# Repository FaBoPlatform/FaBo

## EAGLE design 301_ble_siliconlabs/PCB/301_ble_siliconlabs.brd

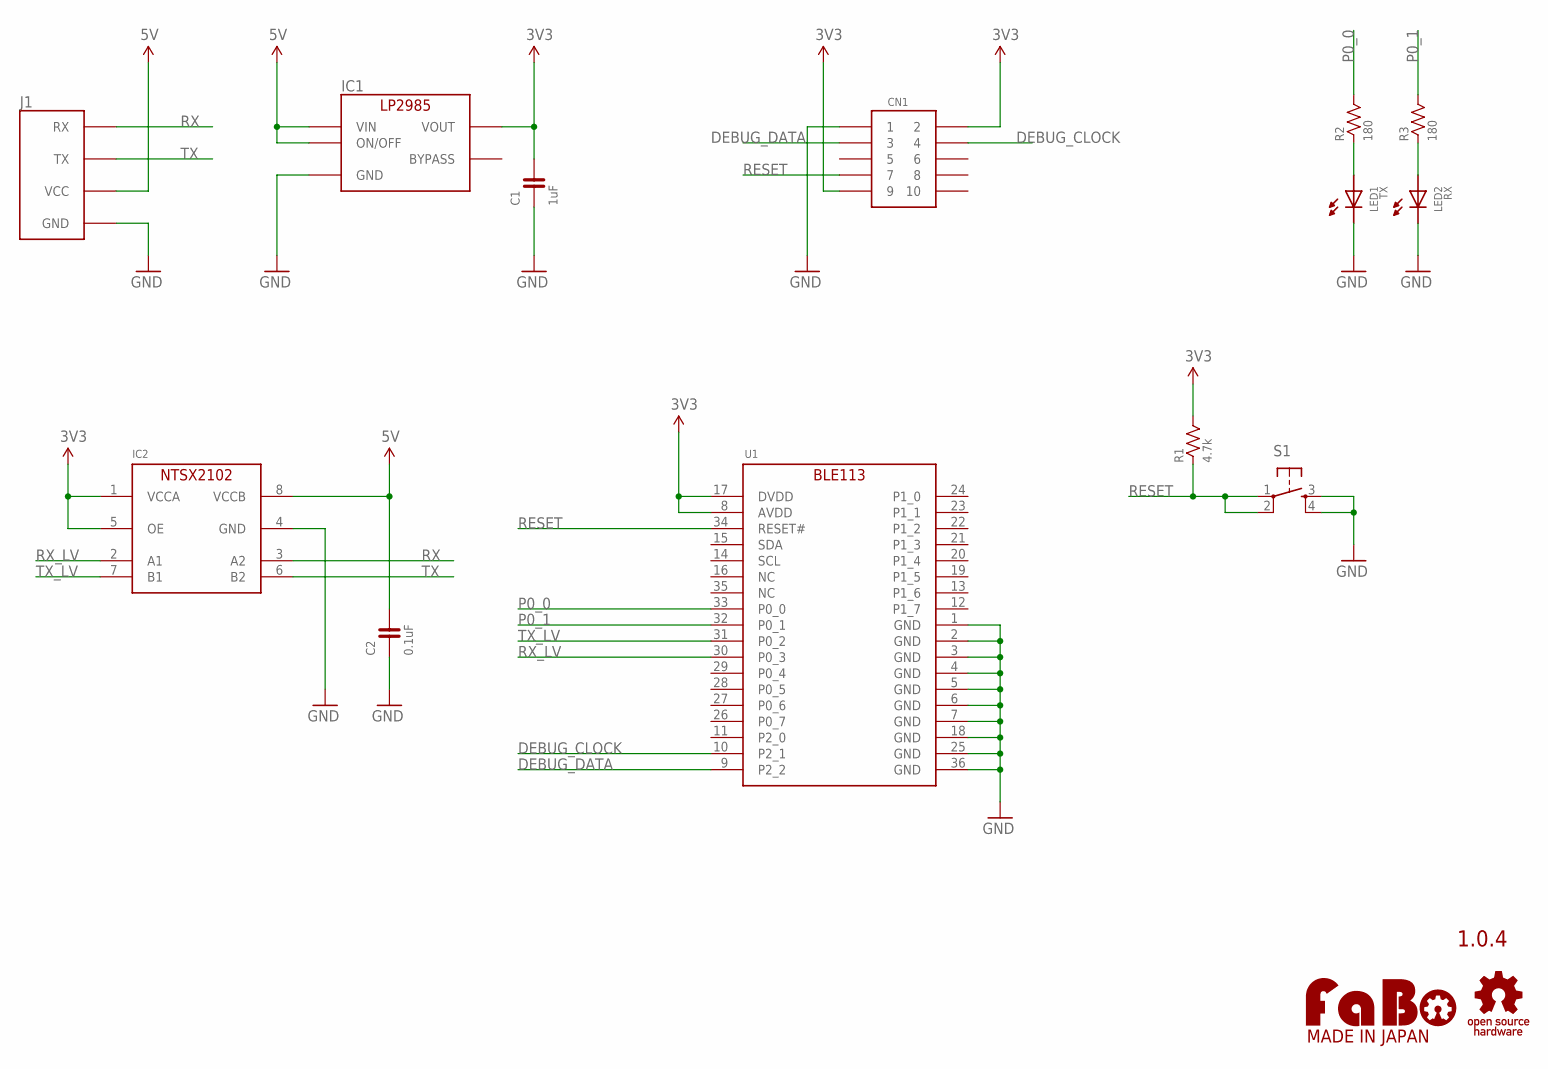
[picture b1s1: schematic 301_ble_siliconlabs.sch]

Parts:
C1: 1uF; 0603
C2: 0.1uF; 0603
CN1: PIN-HEADER-SMT(1.27MM)2X5
IC1: LP2985-33DBV; SOT-23-5
IC2: NTSX2102GU8H; SOT1309-1
J1: FABO_BRICK_SERIAL
LED1: TX; 0603
LED2: RX; 0603
R1: 4.7k; 0603
R2, R3: 180; 0603
S1: TACT-SWITCH-SMD_KMR2; KMR2
U1: BLUEGIGA-BLE113
U$2: LOGO_OSHW-M_BOTTOM; LOGO_OSHW_M_BOTTOM
U$3: LOGO_FABO-M_BOTTOM; LOGO_FABO_MS_BOTTOM

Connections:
3V3: C1.2, CN1.2, CN1.9, IC1.5 (VOUT), IC2.1 (VCCA), IC2.5 (OE), R1.2, U1.8 (AVDD), U1.17 (DVDD)
5V: C2.2, IC1.1 (VIN), IC1.3 (ON/OFF), IC2.8 (VCCB), J1.VCC
DEBUG_CLOCK: CN1.4, U1.10 (P2_1)
DEBUG_DATA: CN1.3, U1.9 (P2_2)
GND: C1.1, C2.1, CN1.1, IC1.2 (GND), IC2.4 (GND), J1.GND, LED1.CATHODE, LED2.CATHODE, S1.3, S1.4, U1.1 (GND), U1.2 (GND), U1.3 (GND), U1.4 (GND), U1.5 (GND), U1.6 (GND), U1.7 (GND), U1.18 (GND), U1.25 (GND), U1.36 (GND)
unnamed: LED1.ANODE, R2.1
unnamed: LED2.ANODE, R3.1
P0_0: R2.2, U1.33 (P0_0)
P0_1: R3.2, U1.32 (P0_1)
RESET: CN1.7, R1.1, S1.1, S1.2, U1.34 (RESET#)
RX: IC2.3 (A2), J1.RX
RX_LV: IC2.2 (A1), U1.30 (P0_3)
TX: IC2.6 (B2), J1.TX
TX_LV: IC2.7 (B1), U1.31 (P0_2)

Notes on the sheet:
1.0.4

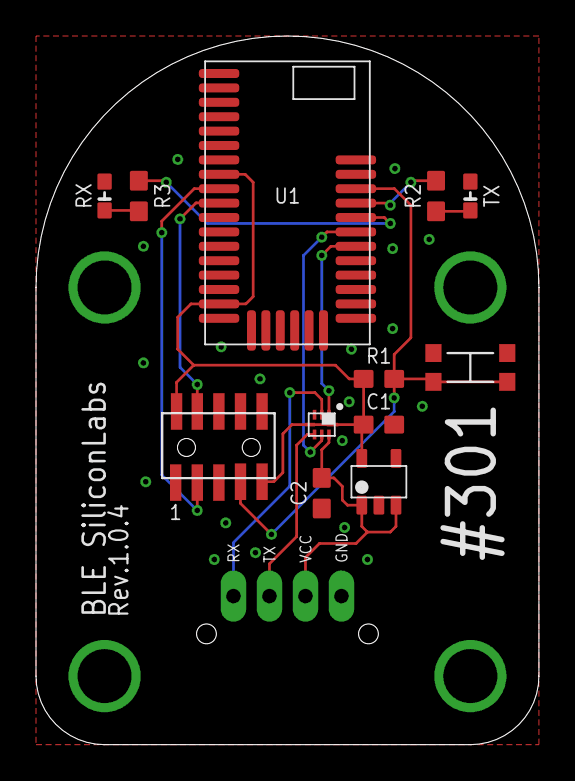
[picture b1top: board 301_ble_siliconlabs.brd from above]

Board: 2 copper layers, 27.9 x 39.4 mm, 15 parts (0 on the bottom side), 14 nets.

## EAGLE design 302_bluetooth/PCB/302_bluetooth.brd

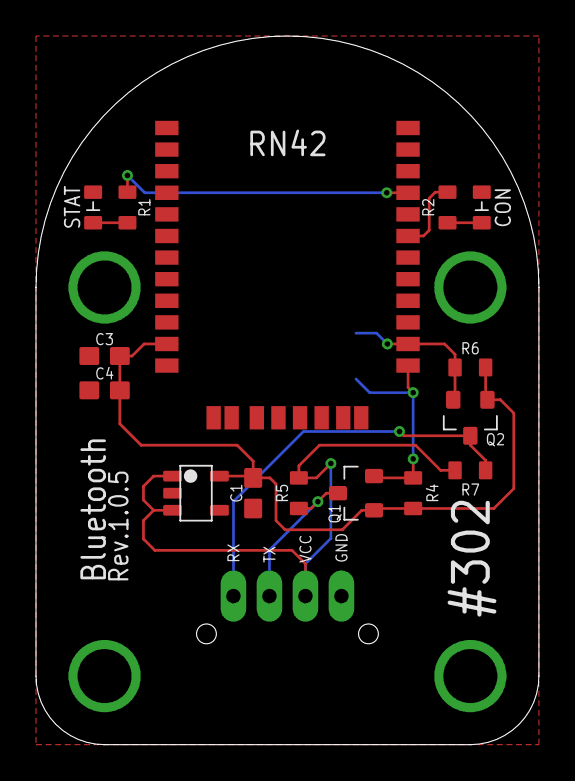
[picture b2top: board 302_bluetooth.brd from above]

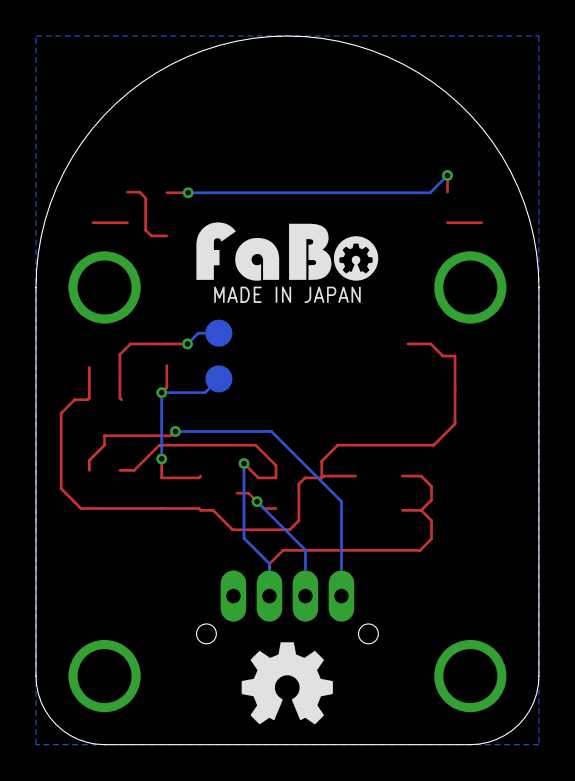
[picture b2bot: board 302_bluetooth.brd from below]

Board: 2 copper layers, 27.9 x 39.4 mm, 20 parts (2 on the bottom side), 11 nets.

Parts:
C1, C4: 1uF; 0603
C3: 0.1uF; 0603
IC1: SOT-23-5
J1: FABO_BRICK_SERIAL
LED1: STAT; 0603-NARROW
LED2: CON; 0603-NARROW
Q1, Q2: BSS138; SOT23-3
R1, R2: 180; 0603-NARROW
R4, R5, R6, R7: 10k; 0603-NARROW
TP10, TP11: TP-15
U$1: MICROCHIP-RN42
U$3: LOGO_FABO_MS_BOTTOM
U$4: LOGO_OSHW_M_BOTTOM

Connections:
3V3: C1.2, C3.2, C4.2, IC1.5, Q1.1, Q2.1, R4.2, R6.2, U$1.11
5V: IC1.1, IC1.3, J1.VCC, R5.2, R7.2
GND: C1.1, C3.1, C4.1, IC1.2, J1.GND, LED1.CATHODE, LED2.CATHODE, U$1.1, U$1.4, U$1.12, U$1.28, U$1.29
unnamed: LED1.ANODE, R1.1
unnamed: R2.2, U$1.19
unnamed: R1.2, U$1.21
unnamed: LED2.ANODE, R2.1
RX: J1.RX, Q2.3, R7.1
RX_LV: Q2.2, R6.1, TP10.1, U$1.14
TX: J1.TX, Q1.3, R5.1
TX_LV: Q1.2, R4.1, TP11.1, U$1.13

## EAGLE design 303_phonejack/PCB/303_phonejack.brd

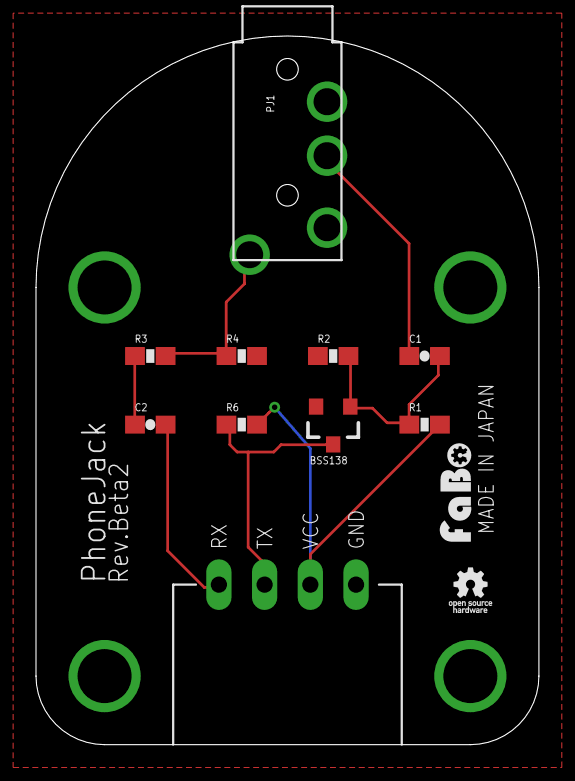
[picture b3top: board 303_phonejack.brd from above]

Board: 2 copper layers, 27.9 x 39.4 mm, 12 parts (0 on the bottom side), 8 nets.

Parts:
BSS138: SOT23-3
C1, C2: 1u; EIA0603-CAP
J1: 0; BRICK_SERIAL
PJ1: MJ-4PP-9; PHONEJACK-MJ-4PP-9
R1: 100k; EIA0603-RES
R2: 22k; EIA0603-RES
R3: 4.7k; EIA0603-RES
R4: 3k; EIA0603-RES
R6: 10K; 0603-RES
U$1: LOGO_FABO_S
U$2: LOGO_OSHW_T_S

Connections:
+5V: J1.VCC, R1.2, R6.2
GND: BSS138.2, J1.GND, PJ1.B, R2.1, R4.2
MIC: PJ1.A, R3.2, R4.1
unnamed: C2.1, R3.1
unnamed: C1.1, PJ1.C
RX: C2.2, J1.RX
TX_HV: BSS138.3, J1.TX, R6.1
TX_LV: BSS138.1, C1.2, R1.1, R2.2

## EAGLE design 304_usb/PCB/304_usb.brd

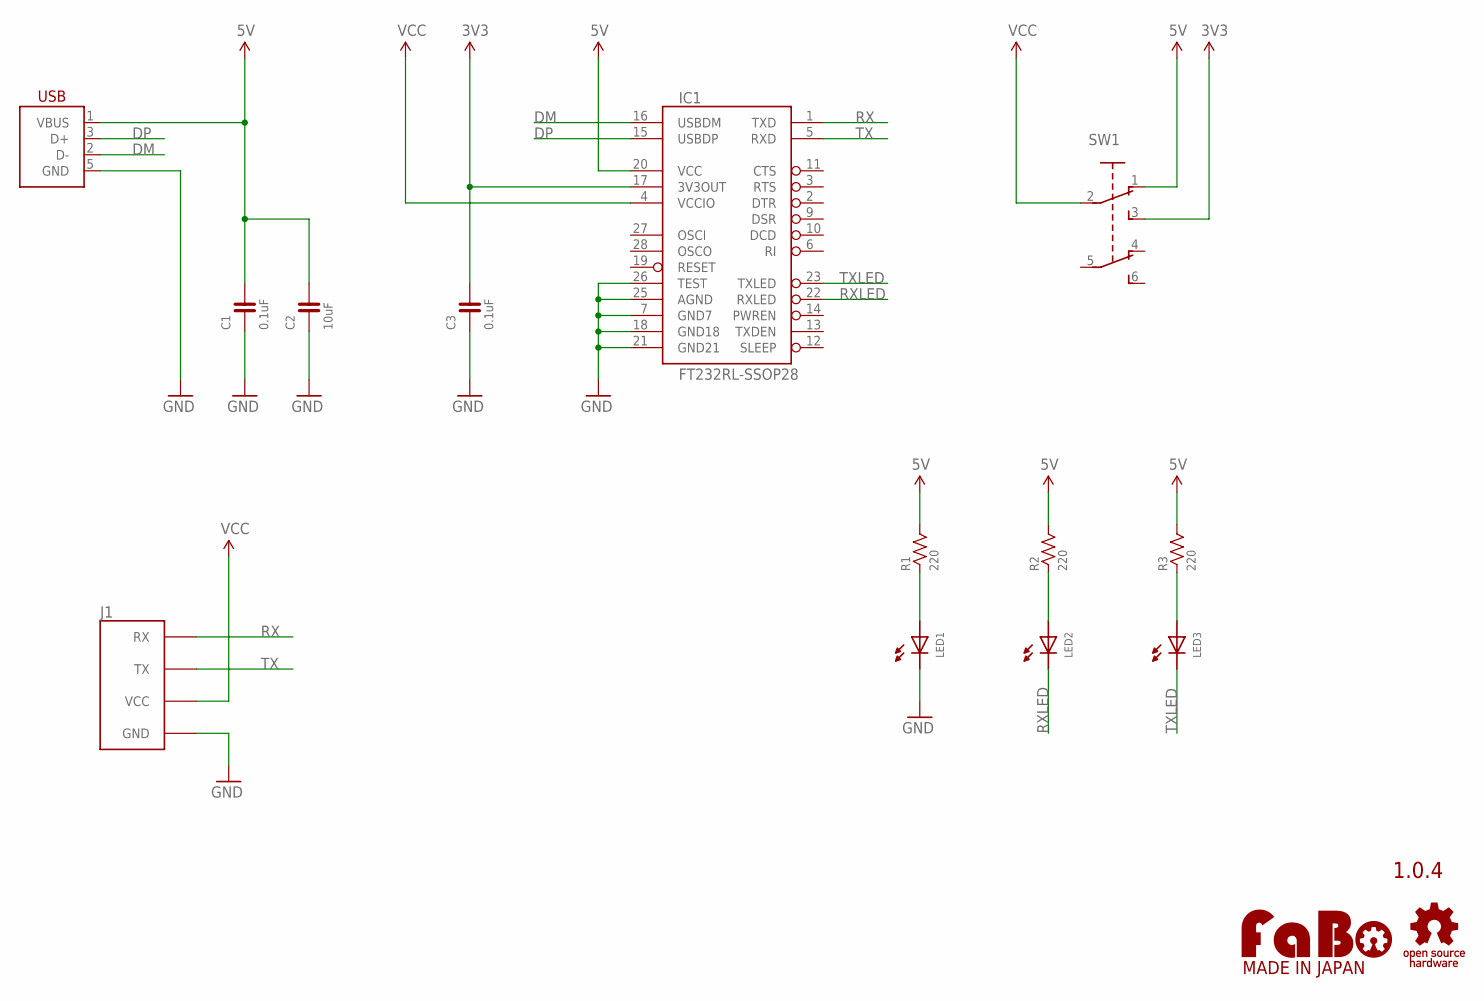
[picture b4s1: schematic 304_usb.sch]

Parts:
C1, C3: 0.1uF; 0603
C2: 10uF; 0603
IC1: FT232RL-SSOP28; SSOP28
J1: FABO_BRICK_SERIAL
JP1: USB-MICRO_B_SMT; DX4R005JJ2R1800
LED1, LED2, LED3: LED-0603; 0603
R1, R2, R3: 220; 0603
SW1: SWITCH-SLIDE_2C2P-JS202011SCQN; C&K_JS202011SCQN
U$5: LOGO_OSHW-M_BOTTOM; LOGO_OSHW_M_BOTTOM
U$6: LOGO_FABO-M_BOTTOM; LOGO_FABO_MS_BOTTOM

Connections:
3V3: C3.2, IC1.17 (3V3OUT), SW1.3
5V: C1.2, C2.2, IC1.20 (VCC), JP1.1 (VBUS), R1.2, R2.2, R3.2, SW1.1
DM: IC1.16 (USBDM), JP1.2 (D-)
DP: IC1.15 (USBDP), JP1.3 (D+)
GND: C1.1, C2.1, C3.1, IC1.7 (GND7), IC1.18 (GND18), IC1.21 (GND21), IC1.25 (AGND), IC1.26 (TEST), J1.GND, JP1.5 (GND), LED1.CATHODE
unnamed: LED1.ANODE, R1.1
unnamed: LED3.ANODE, R3.1
unnamed: LED2.ANODE, R2.1
RX: IC1.1 (TXD), J1.RX
RXLED: IC1.22 (RXLED), LED2.CATHODE
TX: IC1.5 (RXD), J1.TX
TXLED: IC1.23 (TXLED), LED3.CATHODE
VCC: IC1.4 (VCCIO), J1.VCC, SW1.2

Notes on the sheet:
1.0.4

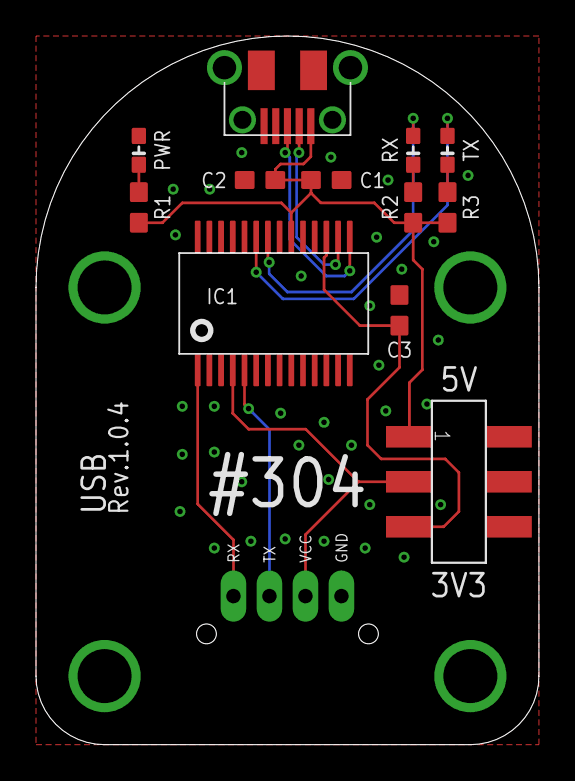
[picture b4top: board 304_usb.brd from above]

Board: 2 copper layers, 27.9 x 39.4 mm, 15 parts (0 on the bottom side), 13 nets.

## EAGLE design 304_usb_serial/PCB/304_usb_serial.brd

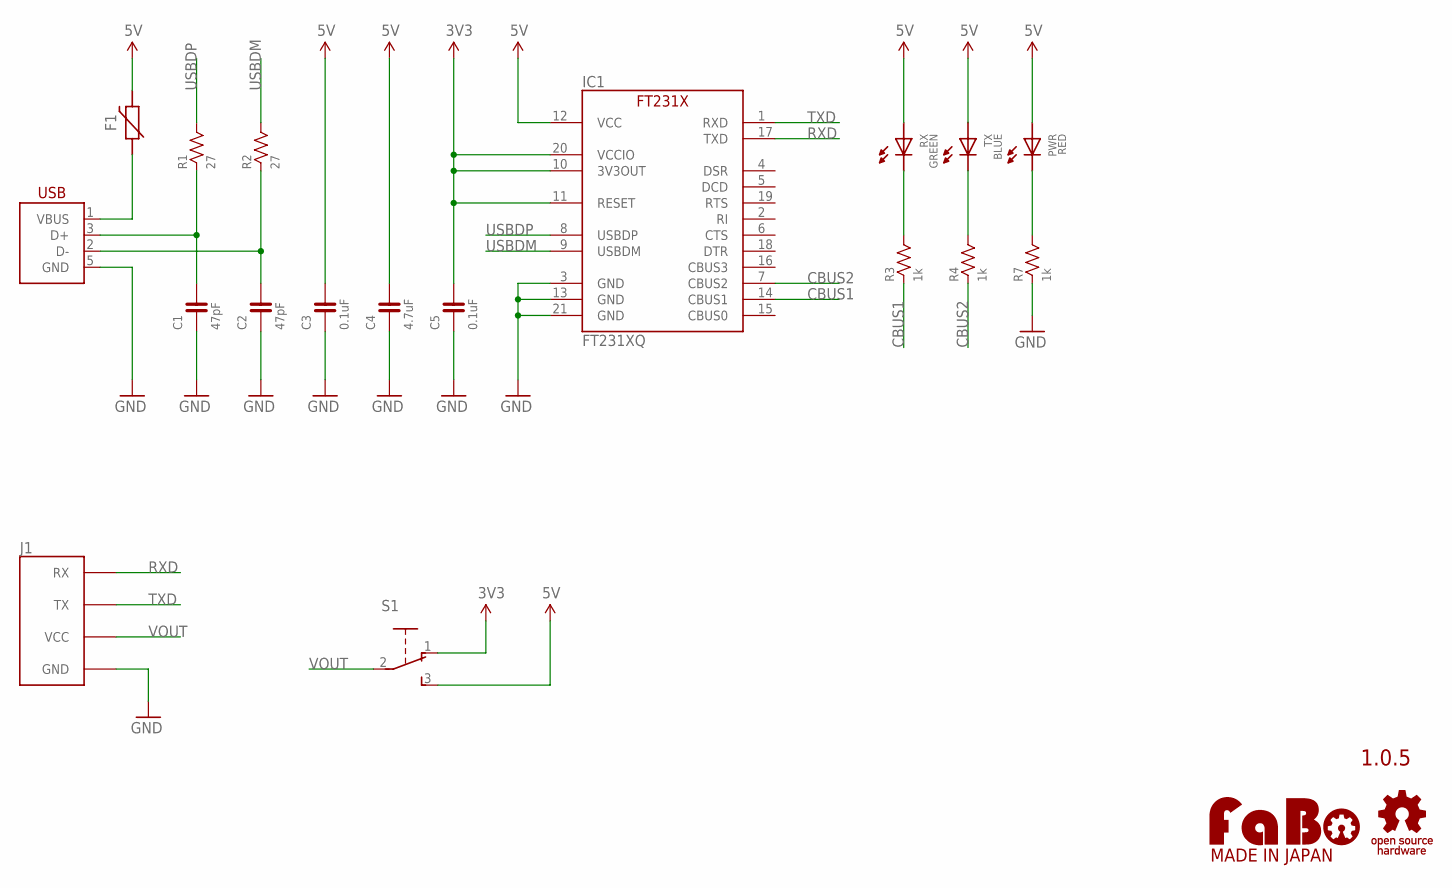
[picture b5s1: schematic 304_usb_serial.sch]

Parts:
C1, C2: 47pF; 0603-NARROW
C3, C5: 0.1uF; 0603-NARROW
C4: 4.7uF; 0603-NARROW
F1: POLYSWITCH; NANOSMDC035F
IC1: FT231XQ; QFN-20_FT231X
J1: FABO_BRICK_SERIAL-USB; FABO_BRICK_SERIAL_USB
PWR: RED; 0603-NARROW
R1, R2: 27; 0603-NARROW
R3, R4, R7: 1k; 0603-NARROW
RX: GREEN; 0603-NARROW
S1: SLIDE-SSSS810701; SSSS810701
TX: BLUE; 0603-NARROW
U$2: LOGO_FABO-M_BOTTOM; LOGO_FABO_MS_BOTTOM
U$3: LOGO_OSHW-M_BOTTOM; LOGO_OSHW_M_BOTTOM
USB1: USB-MICRO_B_SMT_HIROSE; ZX62R-B-5P

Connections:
3V3: C5.2, IC1.10 (3V3OUT), IC1.11 (RESET), IC1.20 (VCCIO), S1.1
5V: C3.2, C4.2, F1.2, IC1.12 (VCC), PWR.ANODE, RX.ANODE, S1.3, TX.ANODE
CBUS1: IC1.14 (CBUS1), R3.1
CBUS2: IC1.7 (CBUS2), R4.1
GND: C1.1, C2.1, C3.1, C4.1, C5.1, IC1.3 (GND), IC1.13 (GND), IC1.21 (GND), J1.GND, R7.1, USB1.5 (GND)
unnamed: PWR.CATHODE, R7.2
unnamed: C2.2, R2.1, USB1.2 (D-)
unnamed: C1.2, R1.1, USB1.3 (D+)
unnamed: R3.2, RX.CATHODE
unnamed: R4.2, TX.CATHODE
RXD: IC1.17 (TXD), J1.RX
TXD: IC1.1 (RXD), J1.TX
USBDM: IC1.9 (USBDM), R2.2
USBDP: IC1.8 (USBDP), R1.2
VBUS: F1.1, USB1.1 (VBUS)
VOUT: J1.VCC, S1.2

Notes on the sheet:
1.0.5

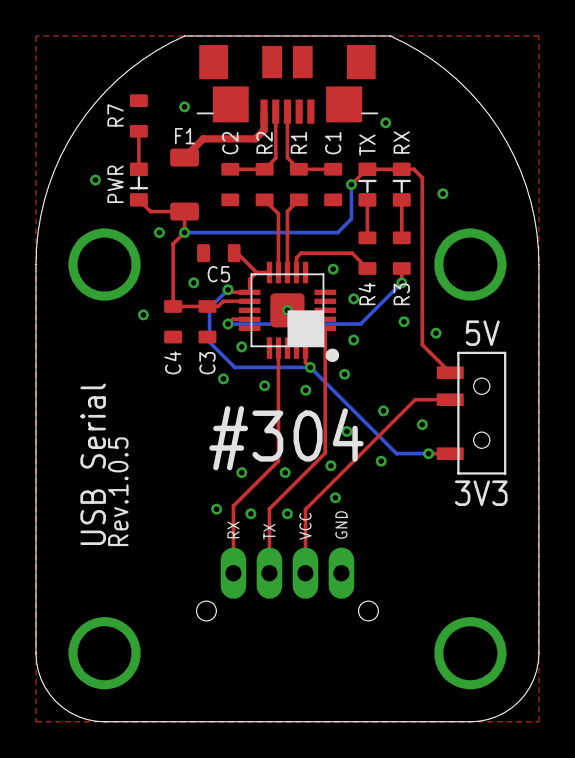
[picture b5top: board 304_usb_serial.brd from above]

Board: 2 copper layers, 27.9 x 38.1 mm, 20 parts (0 on the bottom side), 16 nets.

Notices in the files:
parts and their libraries:
FaBo-etc: Released under the Creative Commons Attribution-ShareAlike 4.0 License
https://creativecommons.org/licenses/by-sa/4.0
FaBo-etc: Released under the Creative Commons
SparkFun: Licensing: CC v3.0 Share-Alike You are welcome to use this library for commercial purposes.
